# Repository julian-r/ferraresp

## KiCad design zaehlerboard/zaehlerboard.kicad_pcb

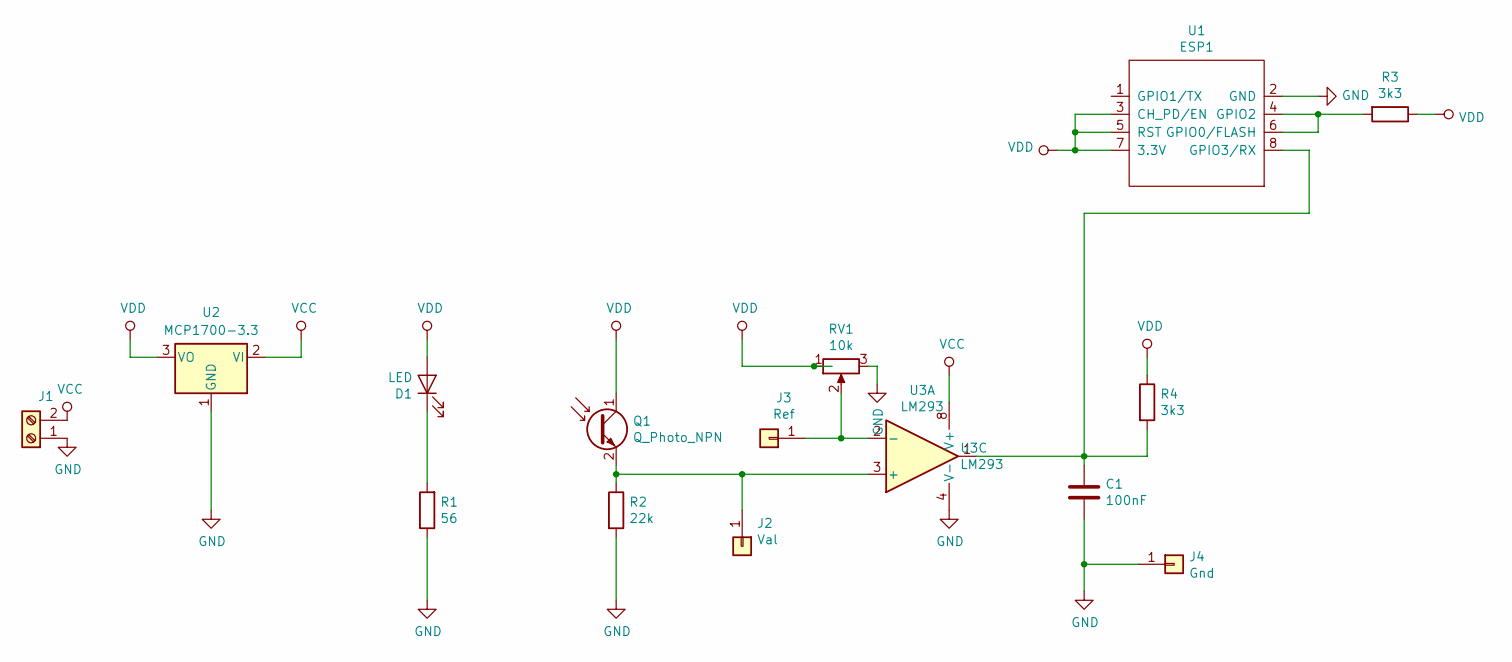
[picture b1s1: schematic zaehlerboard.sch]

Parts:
C1: 100nF; C_Disc_D5.0mm_W2.5mm_P5.00mm
D1: LED; PinHeader_1x02_P2.54mm_Vertical
J1: Screw_Terminal_01x02; TerminalBlock_Altech_AK300-2_P5.00mm
J2: Val; Pin_D0.7mm_L6.5mm_W1.8mm_FlatFork
J3: Ref; Pin_D0.7mm_L6.5mm_W1.8mm_FlatFork
J4: Gnd; Pin_D0.7mm_L6.5mm_W1.8mm_FlatFork
Q1: Q_Photo_NPN; PinHeader_1x02_P2.54mm_Vertical
R1: 56; R_Axial_DIN0204_L3.6mm_D1.6mm_P7.62mm_Horizontal
R2: 22k; R_Axial_DIN0204_L3.6mm_D1.6mm_P7.62mm_Horizontal
R3, R4: 3k3; R_Axial_DIN0204_L3.6mm_D1.6mm_P7.62mm_Horizontal
RV1: 10k; Potentiometer_ACP_CA9-H5_Horizontal
U1: ESP1; PinHeader_2x04_P2.54mm_Vertical
U2: MCP1700-3.3; TO-92
U3: LM293; DIP-8_W7.62mm_Socket

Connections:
GND: C1.2, J1.1, J4.1, R1.1, R2.2, RV1.3, U1.2 (GND), U2.1 (GND), U3.4 (V-)
unnamed: C1.1, R4.2, U1.8 (GPIO3/RX), U3.1
unnamed: D1.1 (K), R1.2
unnamed: J2.1, Q1.2 (E), R2.1, U3.3 (+)
unnamed: J3.1, RV1.2, U3.2 (-)
unnamed: R3.2, U1.4 (GPIO2), U1.6 (GPIO0/FLASH)
VCC: J1.2, U2.2 (VI), U3.8 (V+)
VDD: D1.2 (A), Q1.1 (C), R3.1, R4.1, RV1.1, U1.3 (CH_PD/EN), U1.5 (RST), U1.7 (3.3V), U2.3 (VO)

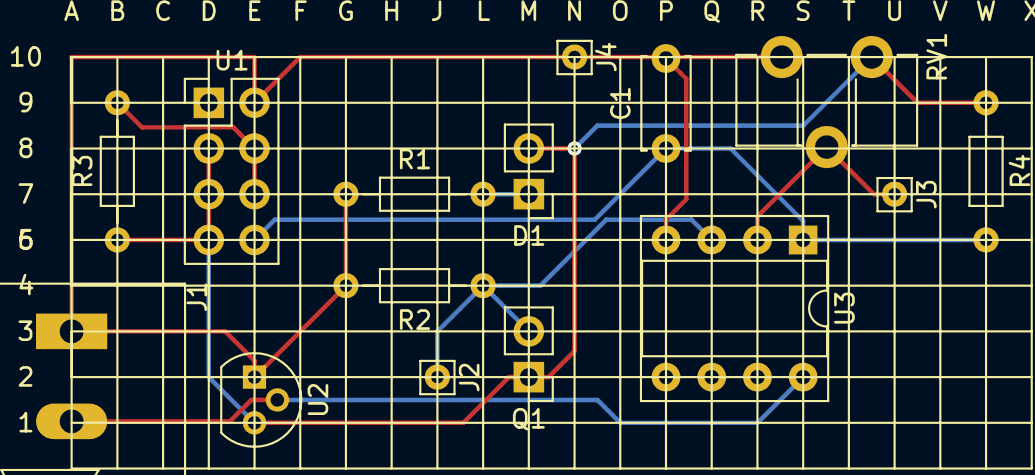
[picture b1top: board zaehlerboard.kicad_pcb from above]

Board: 2 copper layers, 15 parts (0 on the bottom side), 8 nets.

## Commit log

2019-07-24 inital version of firmware
2019-07-28 inital commit
2019-09-23 updated circuit
2019-09-23 extended schematic, added some footprints
2019-09-23 pin associations
2019-09-24 tht mask and fixed esp
2019-10-03 update circuit
2019-10-03 additional elements and new board layout
2019-10-07 pcb changes
2021-09-14 Add .whitesource configuration file
